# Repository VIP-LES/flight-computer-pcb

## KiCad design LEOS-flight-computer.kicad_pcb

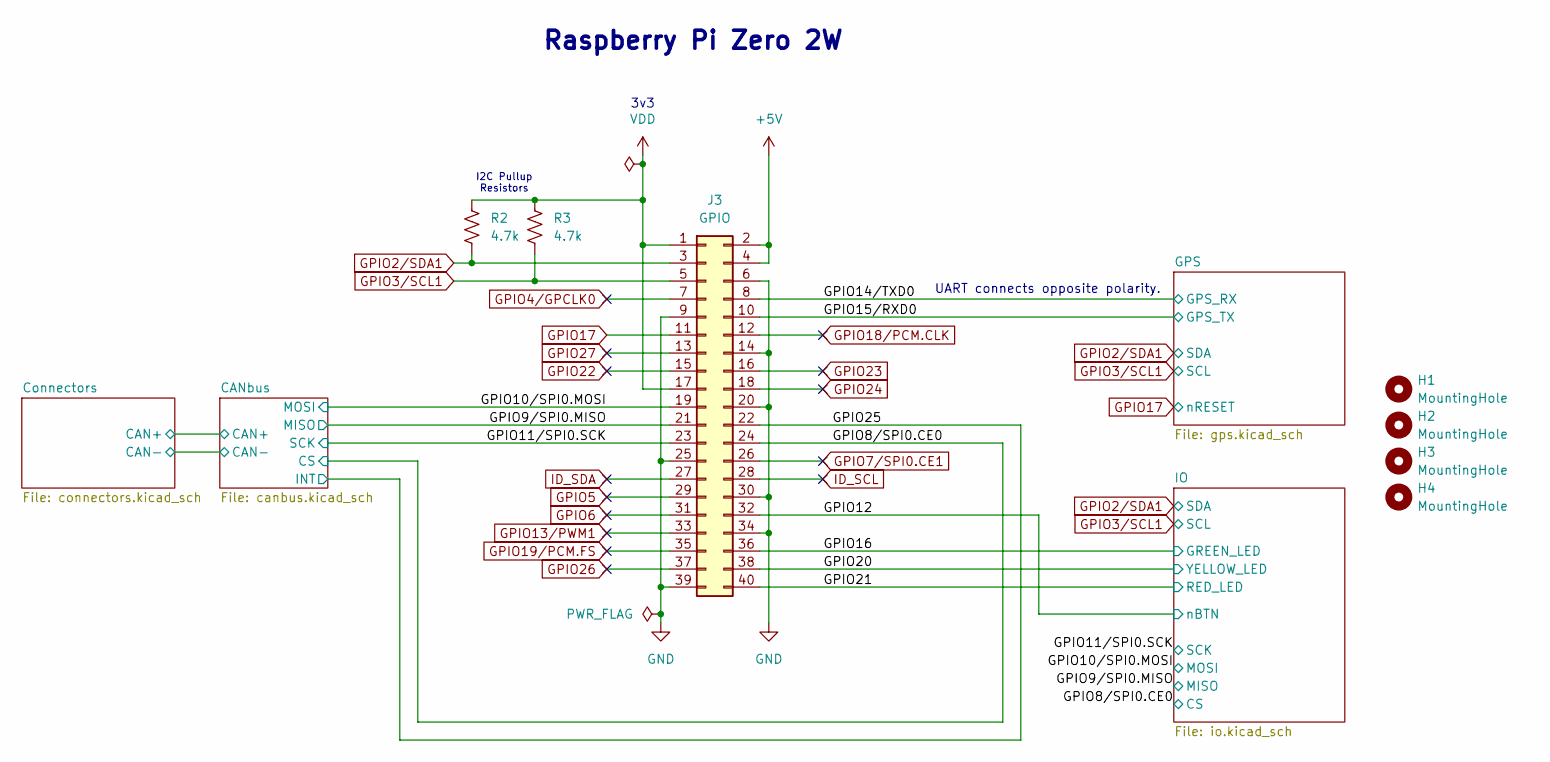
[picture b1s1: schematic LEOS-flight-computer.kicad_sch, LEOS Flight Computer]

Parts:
H1, H2, H3, H4: MountingHole; MountingHole_2.7mm_M2.5
J3: GPIO; PinSocket_2x20_P2.54mm_Vertical
R2, R3: 4.7k; R_0805_2012Metric; MPN CRCW08054K70FKEA; Digikey 541-4.70KCCT-ND

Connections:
+5V: J3.2, J3.4; also elsewhere on the board
/GPIO8/SPI0.CE0: J3.24; also elsewhere on the board
/GPIO9/SPI0.MISO: J3.21; also elsewhere on the board
/GPIO10/SPI0.MOSI: J3.19; also elsewhere on the board
/GPIO11/SPI0.SCK: J3.23; also elsewhere on the board
/GPIO12: J3.32; also elsewhere on the board
/GPIO14/TXD0: J3.8; also elsewhere on the board
/GPIO15/RXD0: J3.10; also elsewhere on the board
/GPIO16: J3.36; also elsewhere on the board
/GPIO20: J3.38; also elsewhere on the board
/GPIO21: J3.40; also elsewhere on the board
/GPIO25: J3.22; also elsewhere on the board
GND: J3.6, J3.9, J3.14, J3.20, J3.25, J3.30, J3.34, J3.39; also elsewhere on the board
GPIO2/SDA1: J3.3, R2.2; also elsewhere on the board
GPIO3/SCL1: J3.5, R3.2; also elsewhere on the board
GPIO4/GPCLK0: J3.7
GPIO5: J3.29
GPIO6: J3.31
GPIO7/SPI0.CE1: J3.26
GPIO13/PWM1: J3.33
GPIO17: J3.11; also elsewhere on the board
GPIO18/PCM.CLK: J3.12
GPIO19/PCM.FS: J3.35
GPIO22: J3.15
GPIO23: J3.16
GPIO24: J3.18
GPIO26: J3.37
GPIO27: J3.13
ID_SCL: J3.28
ID_SDA: J3.27
VDD: J3.1, J3.17, R2.1, R3.1; also elsewhere on the board

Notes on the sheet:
3v3
UART connects opposite polarity.
I2C Pullup Resistors
Raspberry Pi Zero 2W

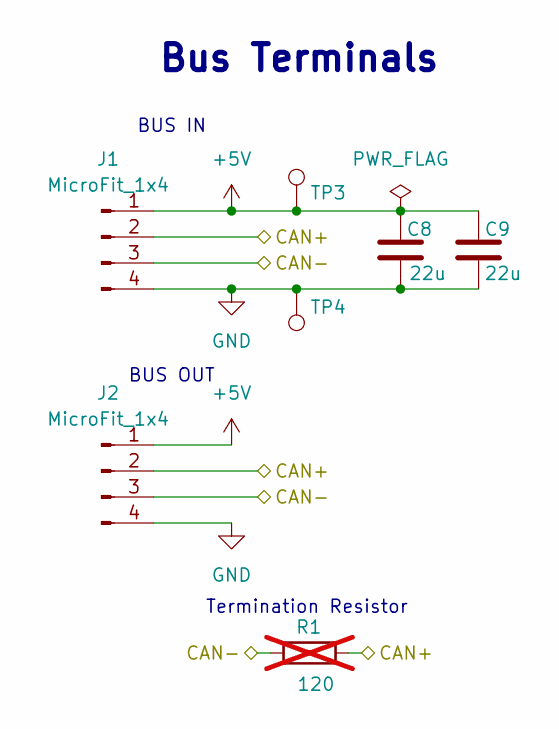
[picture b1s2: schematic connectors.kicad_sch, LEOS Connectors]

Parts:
C8, C9: 22u; C_0805_2012Metric; MPN CL21A226MAYNNNE; Digikey 1276-CL21A226MAYNNNECT-ND
J1, J2: MicroFit_1x4; Molex_MicroFit3.0_43650-0410_1x04_Horizontal; MPN 0436500409; Digikey WM1882CT-ND
R1: 120; R_Axial_DIN0207_L6.3mm_D2.5mm_P7.62mm_Horizontal; MPN CF14JT120R; Digikey CF14JT120RCT-ND; not fitted
TP3: 5V Test Point; TestPoint_Loop_D2.60mm_Drill0.9mm_Beaded; MPN 5000; Digikey 36-5000-ND
TP4: GND Test Point; TestPoint_Loop_D2.60mm_Drill0.9mm_Beaded; MPN 5001; Digikey 36-5001-ND

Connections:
+5V: C8.1, C9.1, J1.1, J2.1, TP3.1; also elsewhere on the board
/CANbus/CAN+: J1.2, J2.2, R1.2; also elsewhere on the board
/CANbus/CAN-: J1.3, J2.3, R1.1; also elsewhere on the board
GND: C8.2, C9.2, J1.4, J2.4, TP4.1; also elsewhere on the board

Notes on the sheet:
BUS OUT
Bus Terminals
BUS IN
Termination Resistor

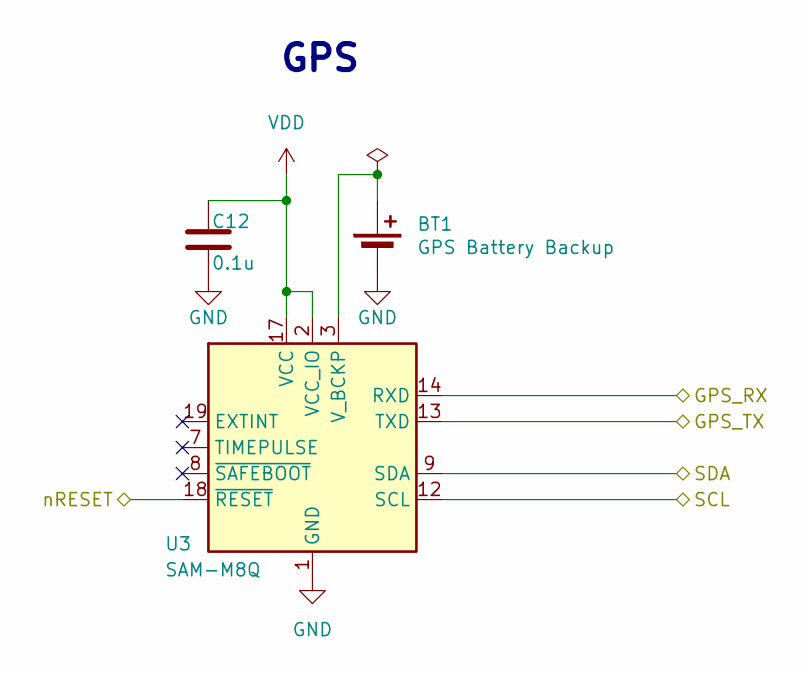
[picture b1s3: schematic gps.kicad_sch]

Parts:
BT1: GPS Battery Backup; BAT_BU2032SM-JJ-GTR; MPN BU2032SM-JJ-GTR; Digikey BU2032SM-JJ-GCT-ND
C12: 0.1u; C_0603_1608Metric; MPN CL10B104KB8NNNL; LCSC C913912
U3: SAM-M8Q; ublox_SAM-M8Q; MPN SAM-M8Q-0; Digikey 672-1054-1-ND

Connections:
/GPIO14/TXD0: U3.14 (RXD); also elsewhere on the board
/GPIO15/RXD0: U3.13 (TXD); also elsewhere on the board
GND: BT1.2 (-), C12.2, U3.1 (GND), U3.4 (GND), U3.5 (GND), U3.6 (GND), U3.10 (GND), U3.11 (GND), U3.15 (GND), U3.16 (GND), U3.20 (GND); also elsewhere on the board
GPIO2/SDA1: U3.9 (SDA); also elsewhere on the board
GPIO3/SCL1: U3.12 (SCL); also elsewhere on the board
GPIO17: U3.18 (~RESET); also elsewhere on the board
unnamed: BT1.1 (+), U3.3 (V_BCKP)
VDD: C12.1, U3.2 (VCC_IO), U3.17 (VCC); also elsewhere on the board

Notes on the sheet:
GPS

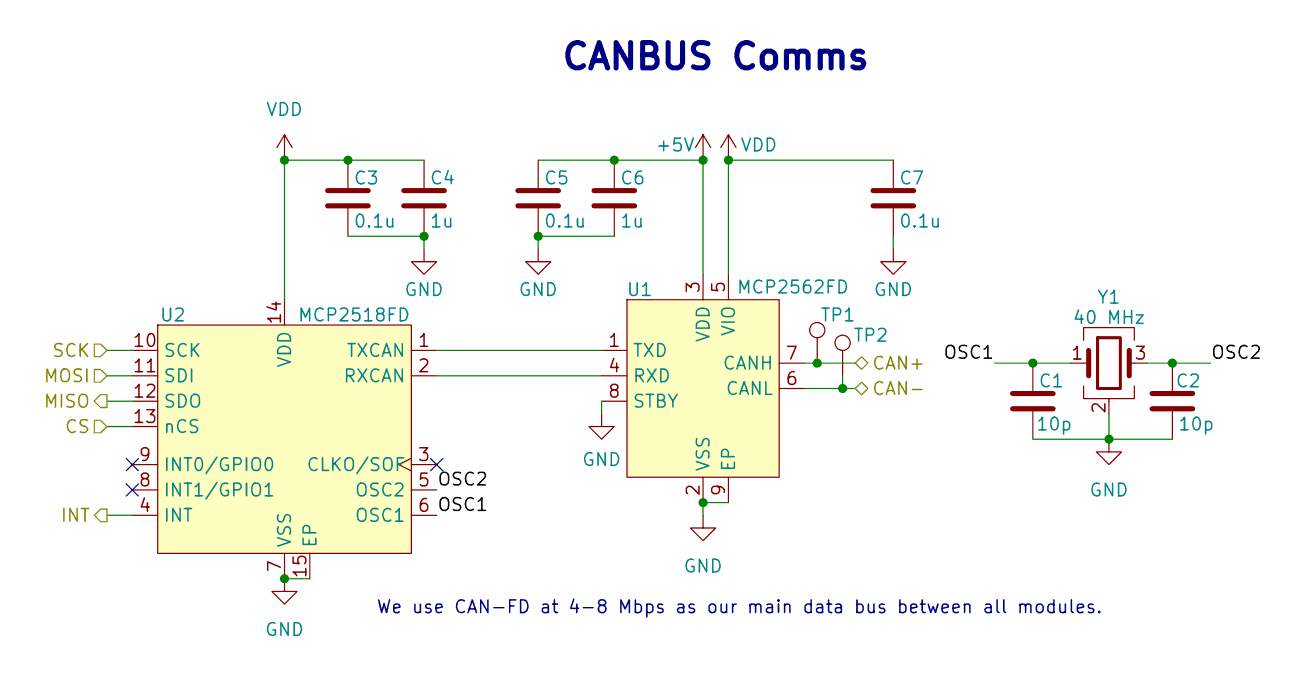
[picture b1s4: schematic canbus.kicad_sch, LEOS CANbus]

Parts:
C1, C2: 10p; C_0603_1608Metric; MPN CL10C100JB8NNNC; Digikey 1276-1027-1-ND
C3, C5, C7: 0.1u; C_0603_1608Metric; MPN CL10B104KB8NNNL; Digikey 1276-CL10B104KB8NNNLCT-ND
C4, C6: 1u; C_0603_1608Metric; MPN CL10B105KA8NNNC; Digikey 1276-1184-1-ND
TP1: CAN-H Test Point; TestPoint_Loop_D2.60mm_Drill0.9mm_Beaded; MPN 5004; Digikey 36-5004-ND
TP2: CAN-L Test Point; TestPoint_Loop_D2.60mm_Drill0.9mm_Beaded; MPN 5116; Digikey 36-5116-ND
U1: MCP2562FD; SOIC-8_3.9x4.9mm_P1.27mm; MPN MCP2562FDT-E/SN; LCSC C511335
U2: MCP2518FD; SOIC-14_3.9x8.7mm_P1.27mm; MPN MCP2518FDT-E/SL; LCSC C626758
Y1: 40 MHz; Crystal_SMD_2016-4Pin_2.0x1.6mm; MPN ECS-400-10-37B2-CKY-TR; Digikey 50-ECS-400-10-37B2-CKY-TRCT-ND

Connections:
+5V: C5.1, C6.1, U1.3 (VDD); also elsewhere on the board
/CANbus/CAN+: TP1.1, U1.7 (CANH); also elsewhere on the board
/CANbus/CAN-: TP2.1, U1.6 (CANL); also elsewhere on the board
/CANbus/OSC1: C1.2, U2.6 (OSC1), Y1.1
/CANbus/OSC2: C2.2, U2.5 (OSC2), Y1.3
/GPIO8/SPI0.CE0: U2.13 (nCS); also elsewhere on the board
/GPIO9/SPI0.MISO: U2.12 (SDO); also elsewhere on the board
/GPIO10/SPI0.MOSI: U2.11 (SDI); also elsewhere on the board
/GPIO11/SPI0.SCK: U2.10 (SCK); also elsewhere on the board
/GPIO25: U2.4 (INT); also elsewhere on the board
GND: C1.1, C2.1, C3.2, C4.2, C5.2, C6.2, C7.2, U1.2 (VSS), U1.8 (STBY), U1.9 (EP), U2.7 (VSS), U2.15 (EP), Y1.2 (G), Y1.4 (G); also elsewhere on the board
unnamed: U1.4 (RXD), U2.2 (RXCAN)
unnamed: U1.1 (TXD), U2.1 (TXCAN)
VDD: C3.1, C4.1, C7.1, U1.5 (VIO), U2.14 (VDD); also elsewhere on the board

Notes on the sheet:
CANBUS Comms
We use CAN-FD at 4-8 Mbps as our main data bus between all modules.

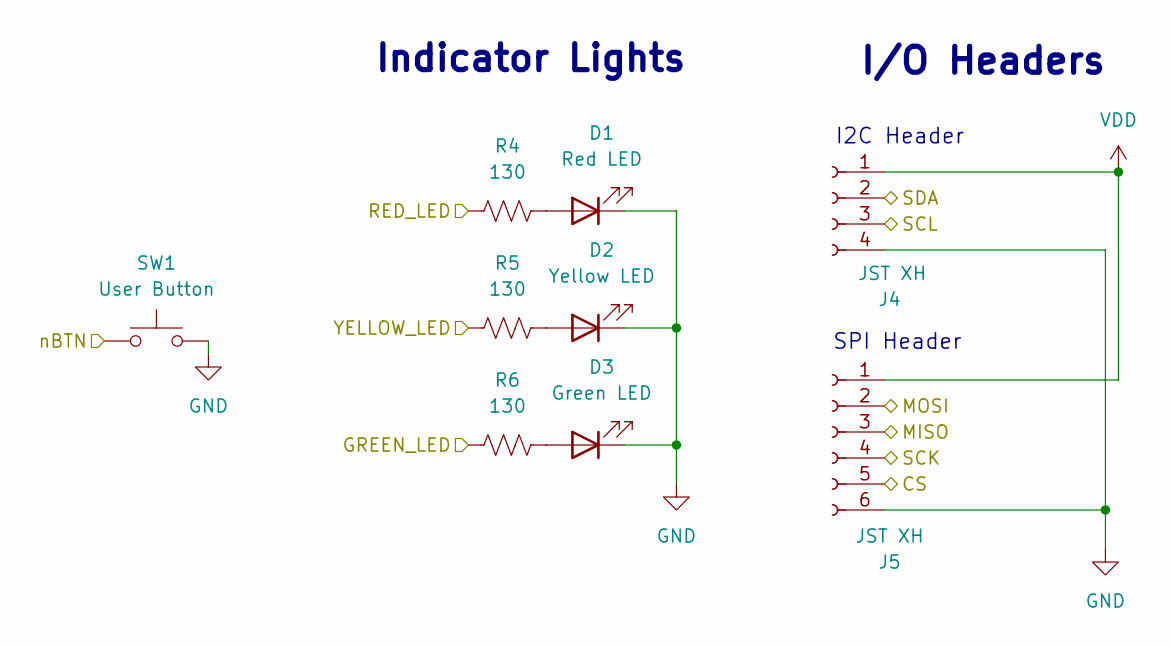
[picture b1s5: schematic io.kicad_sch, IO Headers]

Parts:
D1: Red LED; LED_1206_3216Metric; MPN LTST-C150KRKT; Digikey 160-1405-1-ND
D2: Yellow LED; LED_1206_3216Metric; MPN LTST-C150KSKT; Digikey 160-1406-1-ND
D3: Green LED; LED_1206_3216Metric; MPN LTST-C230KGKT; Digikey 160-1456-1-ND
J4: JST XH; JST_XH_S4B-XH-A_1x04_P2.50mm_Horizontal; MPN S4B-XH-A; Digikey 455-2243-ND
J5: JST XH; JST_XH_S6B-XH-A_1x06_P2.50mm_Horizontal; MPN S6B-XH-A; Digikey 455-S6B-XH-A-ND
R4, R5, R6: 130; R_0805_2012Metric; MPN CRCW0805130RFKEA; Digikey 541-130CCT-ND
SW1: User Button; SW_PUSH_6mm; MPN PTS645SK50-2 LFS; Digikey CKN9082-ND

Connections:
/GPIO8/SPI0.CE0: J5.5; also elsewhere on the board
/GPIO9/SPI0.MISO: J5.3; also elsewhere on the board
/GPIO10/SPI0.MOSI: J5.2; also elsewhere on the board
/GPIO11/SPI0.SCK: J5.4; also elsewhere on the board
/GPIO12: SW1.1; also elsewhere on the board
/GPIO16: R6.1; also elsewhere on the board
/GPIO20: R5.1; also elsewhere on the board
/GPIO21: R4.1; also elsewhere on the board
GND: D1.1 (K), D2.1 (K), D3.1 (K), J4.4, J5.6, SW1.2; also elsewhere on the board
GPIO2/SDA1: J4.2; also elsewhere on the board
GPIO3/SCL1: J4.3; also elsewhere on the board
unnamed: D1.2 (A), R4.2
unnamed: D2.2 (A), R5.2
unnamed: D3.2 (A), R6.2
VDD: J4.1, J5.1; also elsewhere on the board

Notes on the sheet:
SPI Header
I2C Header
Indicator Lights
I/O Headers

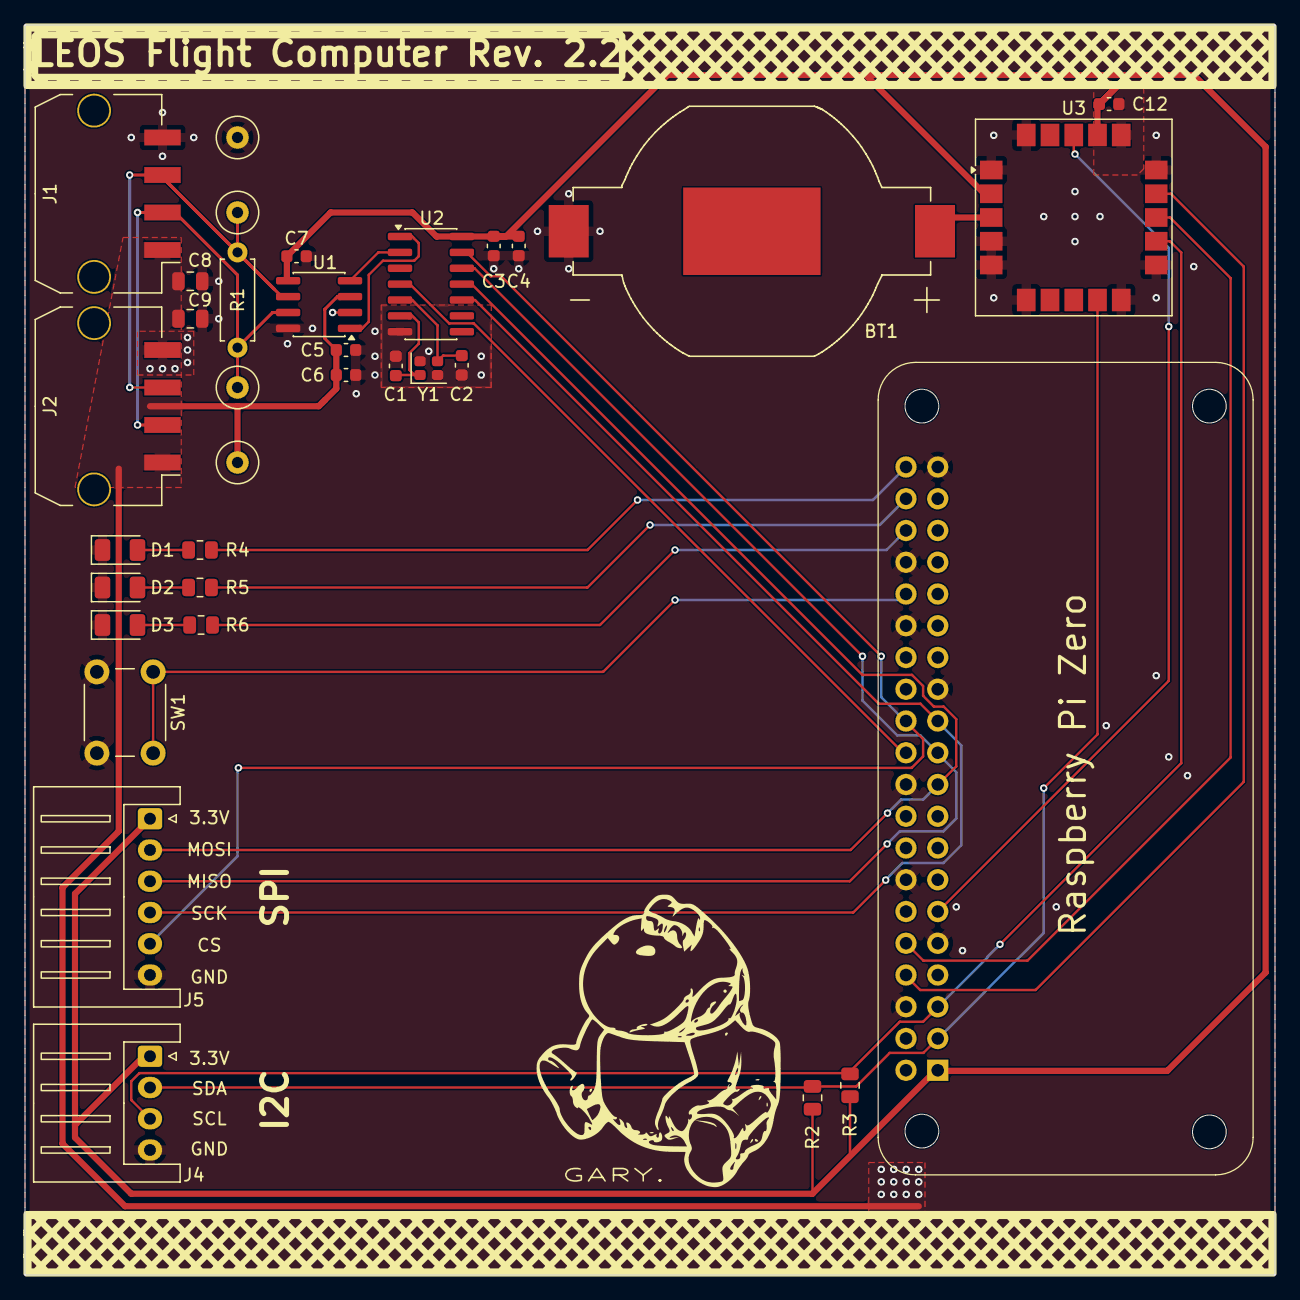
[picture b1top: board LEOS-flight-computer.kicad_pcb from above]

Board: 2 copper layers, 100.0 x 100.0 mm, 38 parts (1 on the bottom side), 27 nets.

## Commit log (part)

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2025-09-15 Updated Initial Layout
2025-09-15 Change Silkscreen name to flight computer
2025-09-15 Corrected layout for flight computer with breakout headers routed
2025-09-17 I routed and schematiced the gps model (SAM-M8Q).
2025-09-17 Added no connects to the pins on the gps module that we aren't using.
2025-09-22 Routed and schematiced a coin cell bettery that is connected to V backup on the gps module
2025-09-27 added footprint for better battery holder
2025-09-27 changed the battery holder to a better one
2025-09-30 Added labels and CANBus SPI connections
2025-09-30 Added part numbers
2025-09-30 Added manufacturers and MPNs for the parts
2025-10-01 Final updates before production - Includes GARY.
2026-02-17 v2.1 with redesigned board, connectors, and improved access to RPi
2026-02-17 remove prl from VC
2026-02-17 Change output dirs for fabrication
2026-02-17 Add .gitignore for KiCad and backup files
2026-02-18 v2.2 with added indicator LEDs and a user button
